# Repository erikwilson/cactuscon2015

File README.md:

# cactuscon2015
Badge design for CactusCon 2015

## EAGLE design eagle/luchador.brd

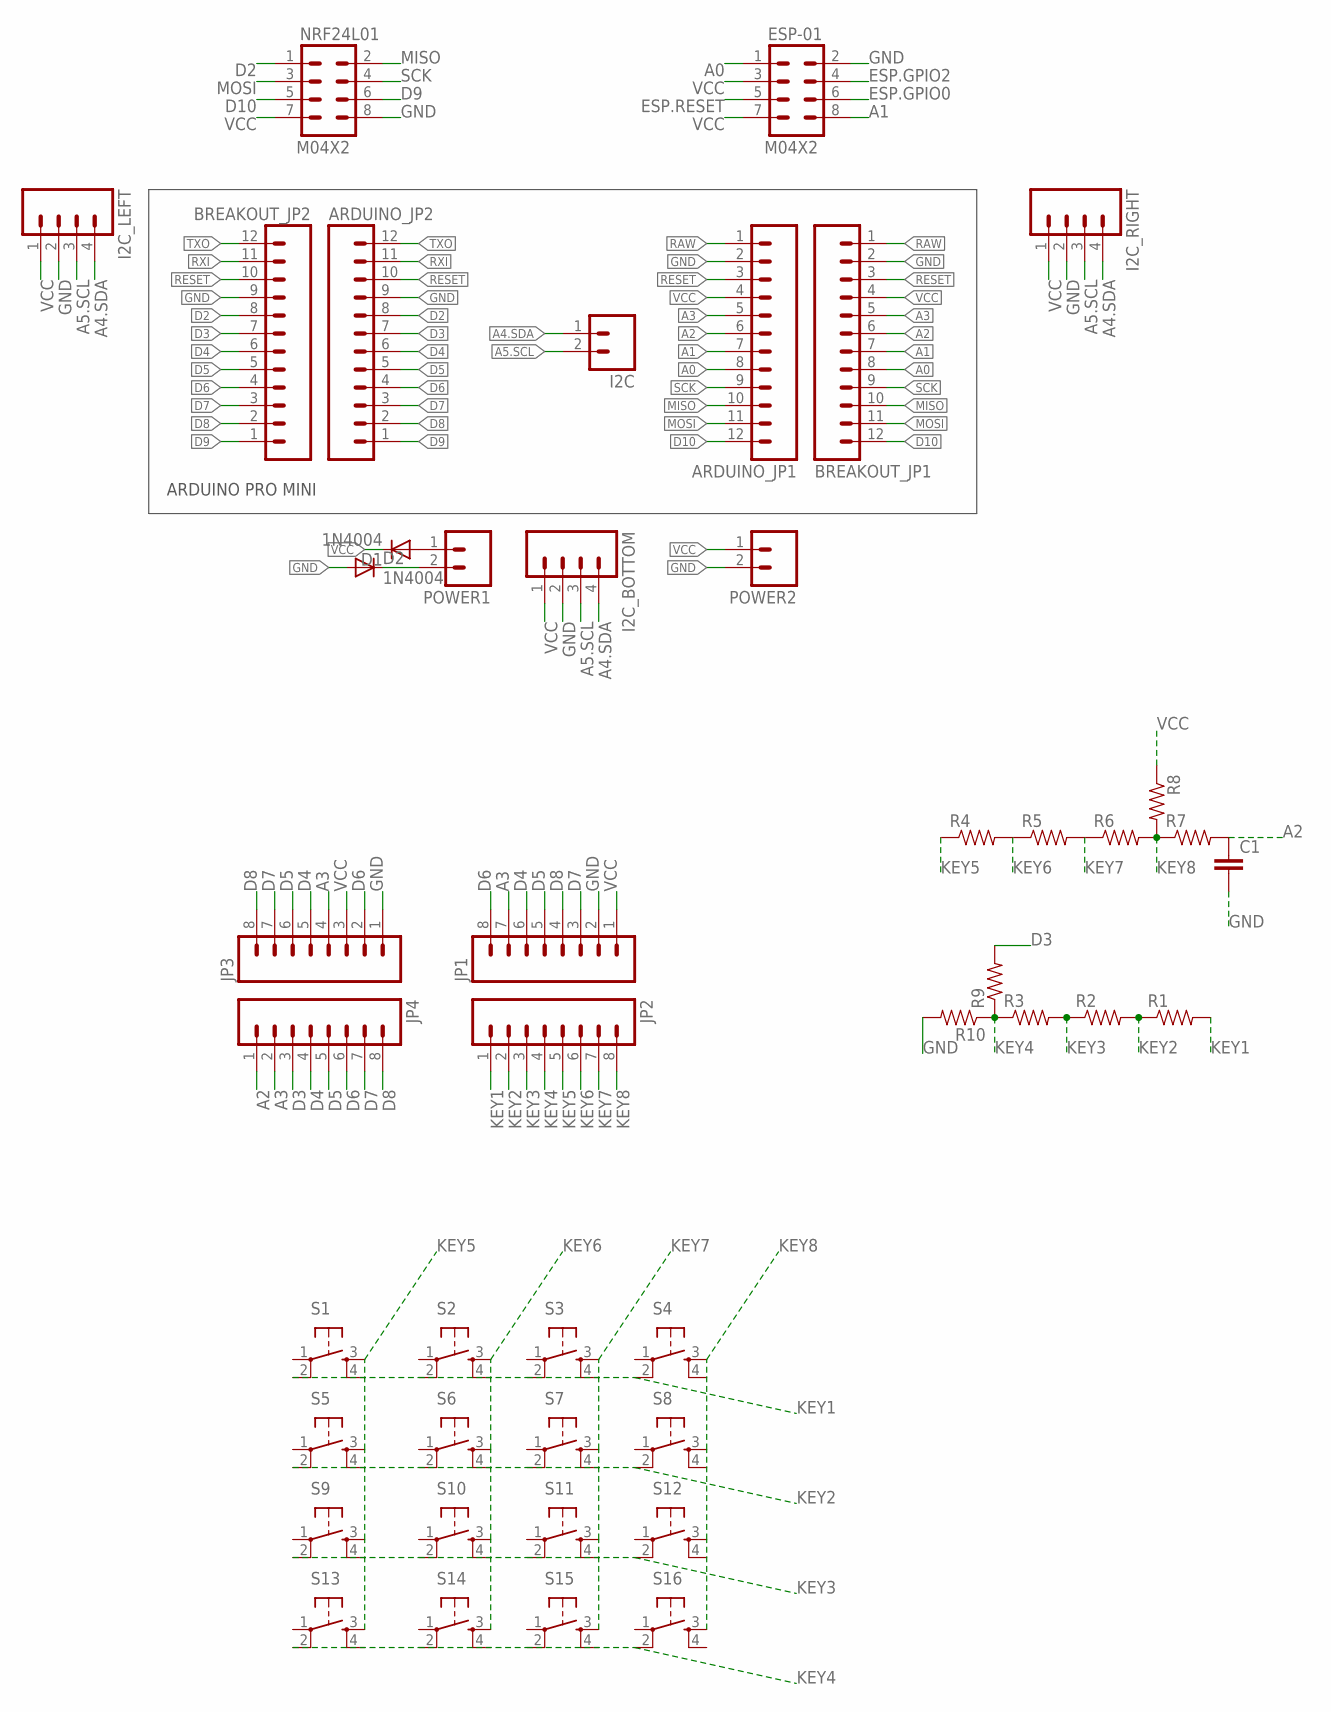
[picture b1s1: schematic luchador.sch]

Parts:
ARDUINO_JP1, ARDUINO_JP2: M12PTH; 1X12
BREAKOUT_JP1, BREAKOUT_JP2: M12PTH; 1X12
C1: CAP_; AXIAL-5MM
D1, D2: 1N4004; DO41-10
ESP-01: M04X2; 2X4
I2C: M02PTH; 1X02
I2C_BOTTOM, I2C_LEFT, I2C_RIGHT: M04PTH; 1X04
JP1, JP2, JP3, JP4: M08SILK_FEMALE_PTH; 1X08
NRF24L01: M04X2; 2X4
POWER1, POWER2: M02PTH; 1X02
R1, R2, R3, R4, R5, R6, R7, R8, R9, R10: RESISTORAXIAL-0.3; AXIAL-0.3
S1, S2, S3, S4, S5, S6, S7, S8, S9, S10, S11, S12, S13, S14, S15, S16: TAC_SWITCHPTH; TACTILE-PTH

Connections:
A0: ARDUINO_JP1.8, BREAKOUT_JP1.8, ESP-01.1
A1: ARDUINO_JP1.7, BREAKOUT_JP1.7, ESP-01.8
A2: ARDUINO_JP1.6, BREAKOUT_JP1.6, C1.P$1 (1), JP4.1, R7.P$2 (2)
A3: ARDUINO_JP1.5, BREAKOUT_JP1.5, JP1.7, JP3.4, JP4.2
A4.SDA: I2C.1, I2C_BOTTOM.4, I2C_LEFT.4, I2C_RIGHT.4
A5.SCL: I2C.2, I2C_BOTTOM.3, I2C_LEFT.3, I2C_RIGHT.3
D2: ARDUINO_JP2.8, BREAKOUT_JP2.8, NRF24L01.1
D3: ARDUINO_JP2.7, BREAKOUT_JP2.7, JP4.3, R9.P$2 (2)
D4: ARDUINO_JP2.6, BREAKOUT_JP2.6, JP1.6, JP3.5, JP4.4
D5: ARDUINO_JP2.5, BREAKOUT_JP2.5, JP1.5, JP3.6, JP4.5
D6: ARDUINO_JP2.4, BREAKOUT_JP2.4, JP1.8, JP3.2, JP4.6
D7: ARDUINO_JP2.3, BREAKOUT_JP2.3, JP1.3, JP3.7, JP4.7
D8: ARDUINO_JP2.2, BREAKOUT_JP2.2, JP1.4, JP3.8, JP4.8
D9: ARDUINO_JP2.1, BREAKOUT_JP2.1, NRF24L01.6
D10: ARDUINO_JP1.12, BREAKOUT_JP1.12, NRF24L01.5
ESP.GPIO0: ESP-01.6
ESP.GPIO2: ESP-01.4
ESP.RESET: ESP-01.5
GND: ARDUINO_JP1.2, ARDUINO_JP2.9, BREAKOUT_JP1.2, BREAKOUT_JP2.9, C1.P$2 (2), D2.A, ESP-01.2, I2C_BOTTOM.2, I2C_LEFT.2, I2C_RIGHT.2, JP1.2, JP3.1, NRF24L01.8, POWER2.2, R10.P$2 (2)
KEY1: JP2.1, R1.P$2 (2), S1.2, S2.2, S3.2, S4.2
KEY2: JP2.2, R1.P$1 (1), R2.P$2 (2), S5.2, S6.2, S7.2, S8.2
KEY3: JP2.3, R2.P$1 (1), R3.P$2 (2), S9.2, S10.2, S11.2, S12.2
KEY4: JP2.4, R3.P$1 (1), R9.P$1 (1), R10.P$1 (1), S13.2, S14.2, S15.2, S16.2
KEY5: JP2.5, R4.P$1 (1), S1.3, S5.3, S9.3, S13.3
KEY6: JP2.6, R4.P$2 (2), R5.P$1 (1), S2.3, S6.3, S10.3, S14.3
KEY7: JP2.7, R5.P$2 (2), R6.P$1 (1), S3.3, S7.3, S11.3, S15.3
KEY8: JP2.8, R6.P$2 (2), R7.P$1 (1), R8.P$2 (2), S4.3, S8.3, S12.3, S16.3
MISO: ARDUINO_JP1.10, BREAKOUT_JP1.10, NRF24L01.2
MOSI: ARDUINO_JP1.11, BREAKOUT_JP1.11, NRF24L01.3
unnamed: D2.C, POWER1.2
unnamed: D1.A, POWER1.1
RAW: ARDUINO_JP1.1, BREAKOUT_JP1.1
RESET: ARDUINO_JP1.3, ARDUINO_JP2.10, BREAKOUT_JP1.3, BREAKOUT_JP2.10
RXI: ARDUINO_JP2.11, BREAKOUT_JP2.11
SCK: ARDUINO_JP1.9, BREAKOUT_JP1.9, NRF24L01.4
TXO: ARDUINO_JP2.12, BREAKOUT_JP2.12
VCC: ARDUINO_JP1.4, BREAKOUT_JP1.4, D1.C, ESP-01.3, ESP-01.7, I2C_BOTTOM.1, I2C_LEFT.1, I2C_RIGHT.1, JP1.1, JP3.3, NRF24L01.7, POWER2.1, R8.P$1 (1)

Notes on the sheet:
ARDUINO PRO MINI

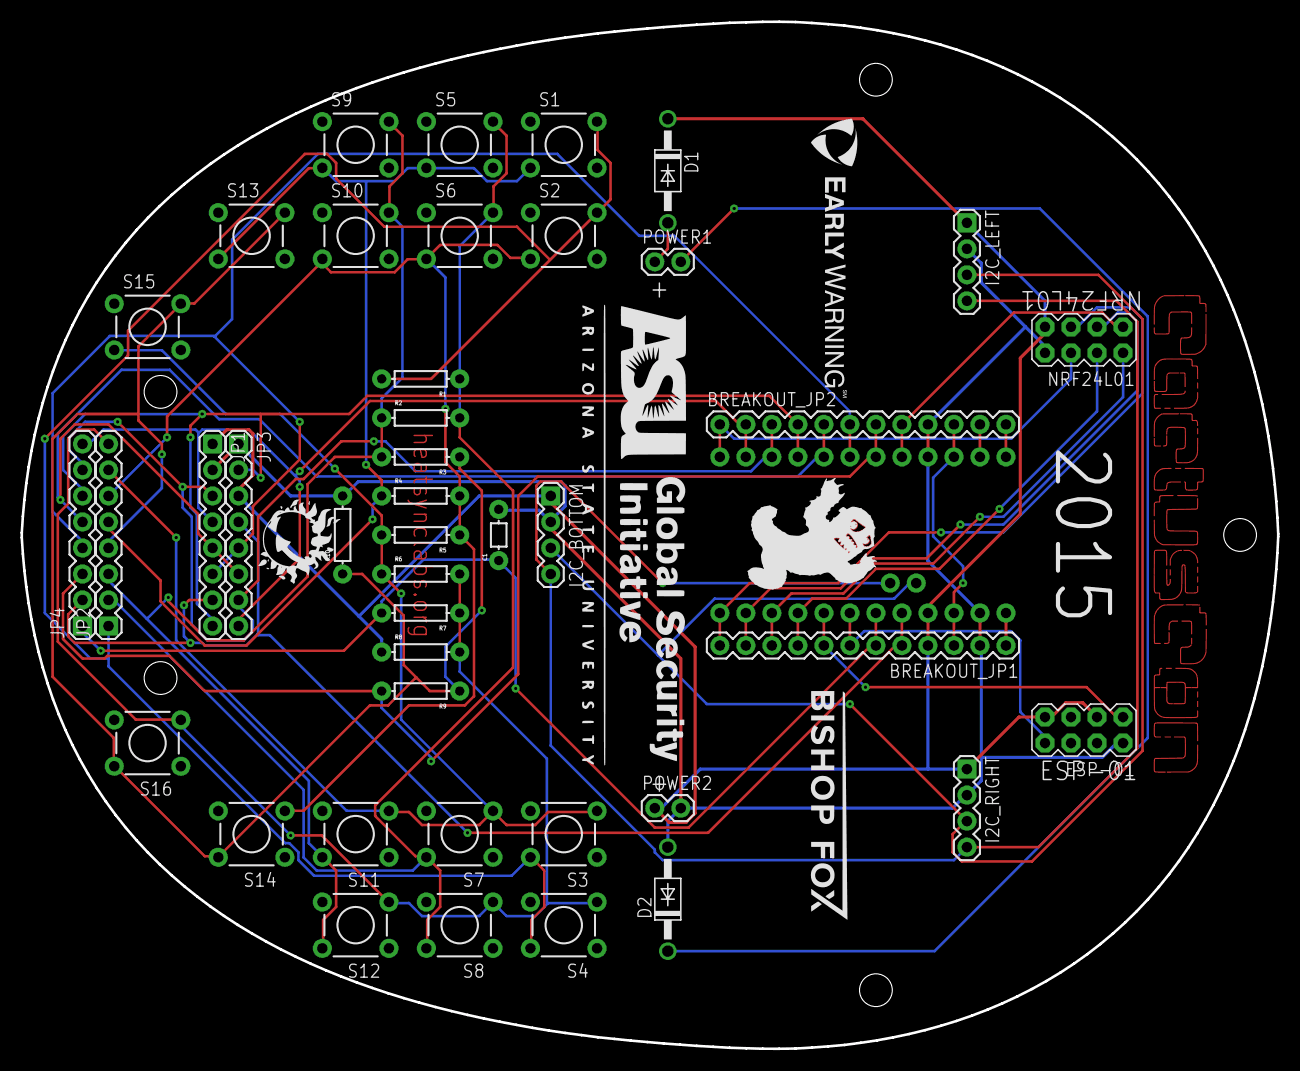
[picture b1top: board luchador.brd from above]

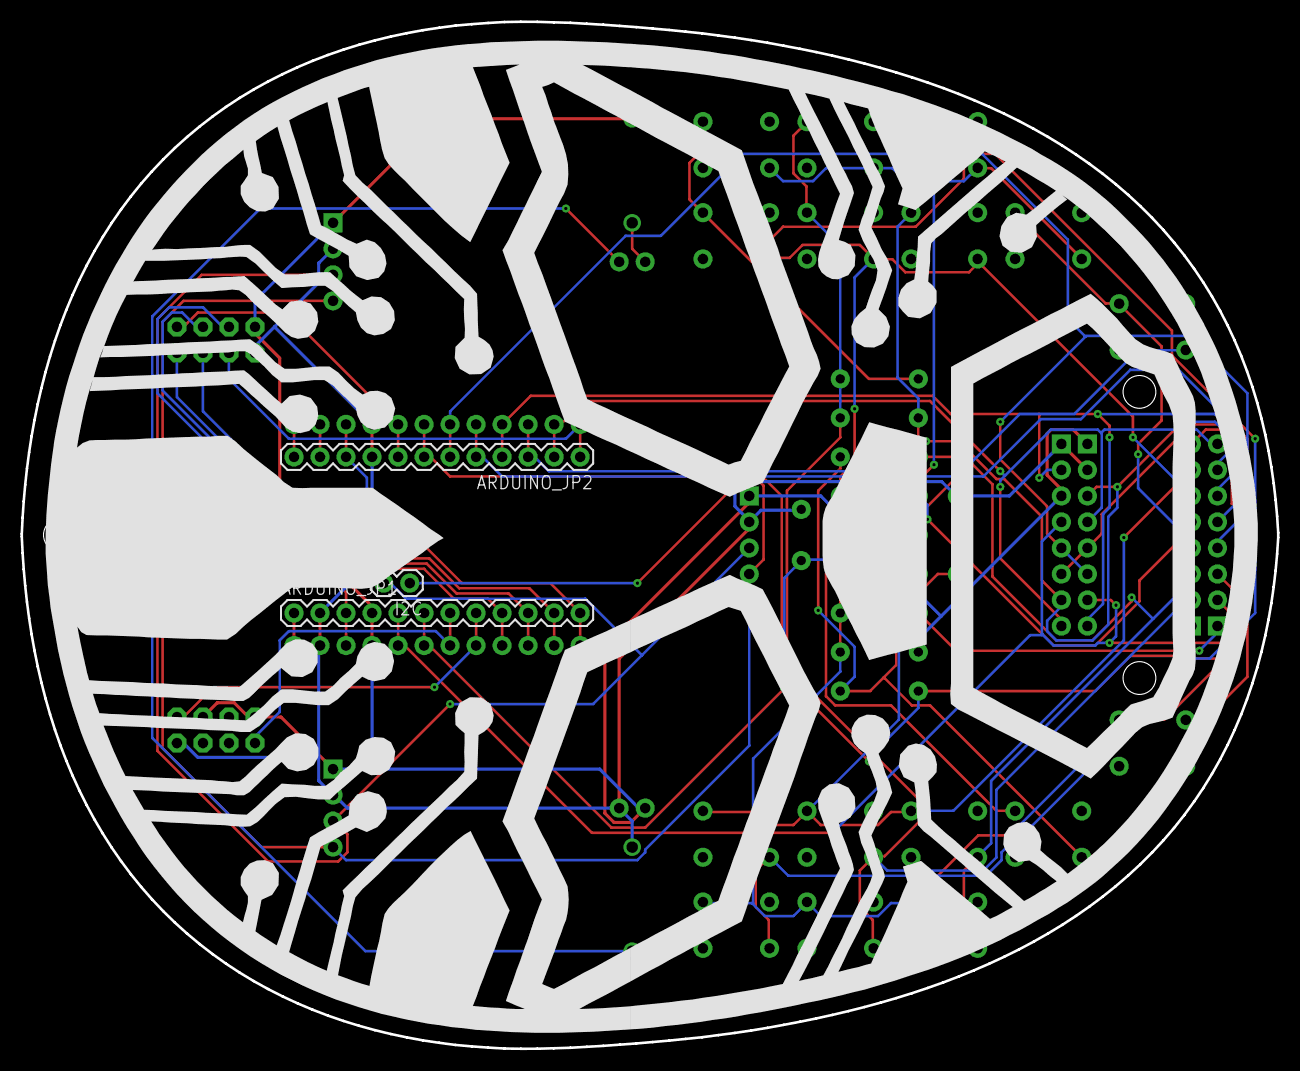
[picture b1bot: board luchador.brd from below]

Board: 2 copper layers, 122.7 x 100.3 mm, 45 parts (3 on the bottom side), 34 nets.

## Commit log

2015-03-13 eagle & gerber files
2015-03-13 stuffs

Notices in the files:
parts and their libraries:
SparkFun-Connectors: Licensing: Creative Commons ShareAlike 4.0 International - https://creativecommons.org/licenses/by-sa/4.0
